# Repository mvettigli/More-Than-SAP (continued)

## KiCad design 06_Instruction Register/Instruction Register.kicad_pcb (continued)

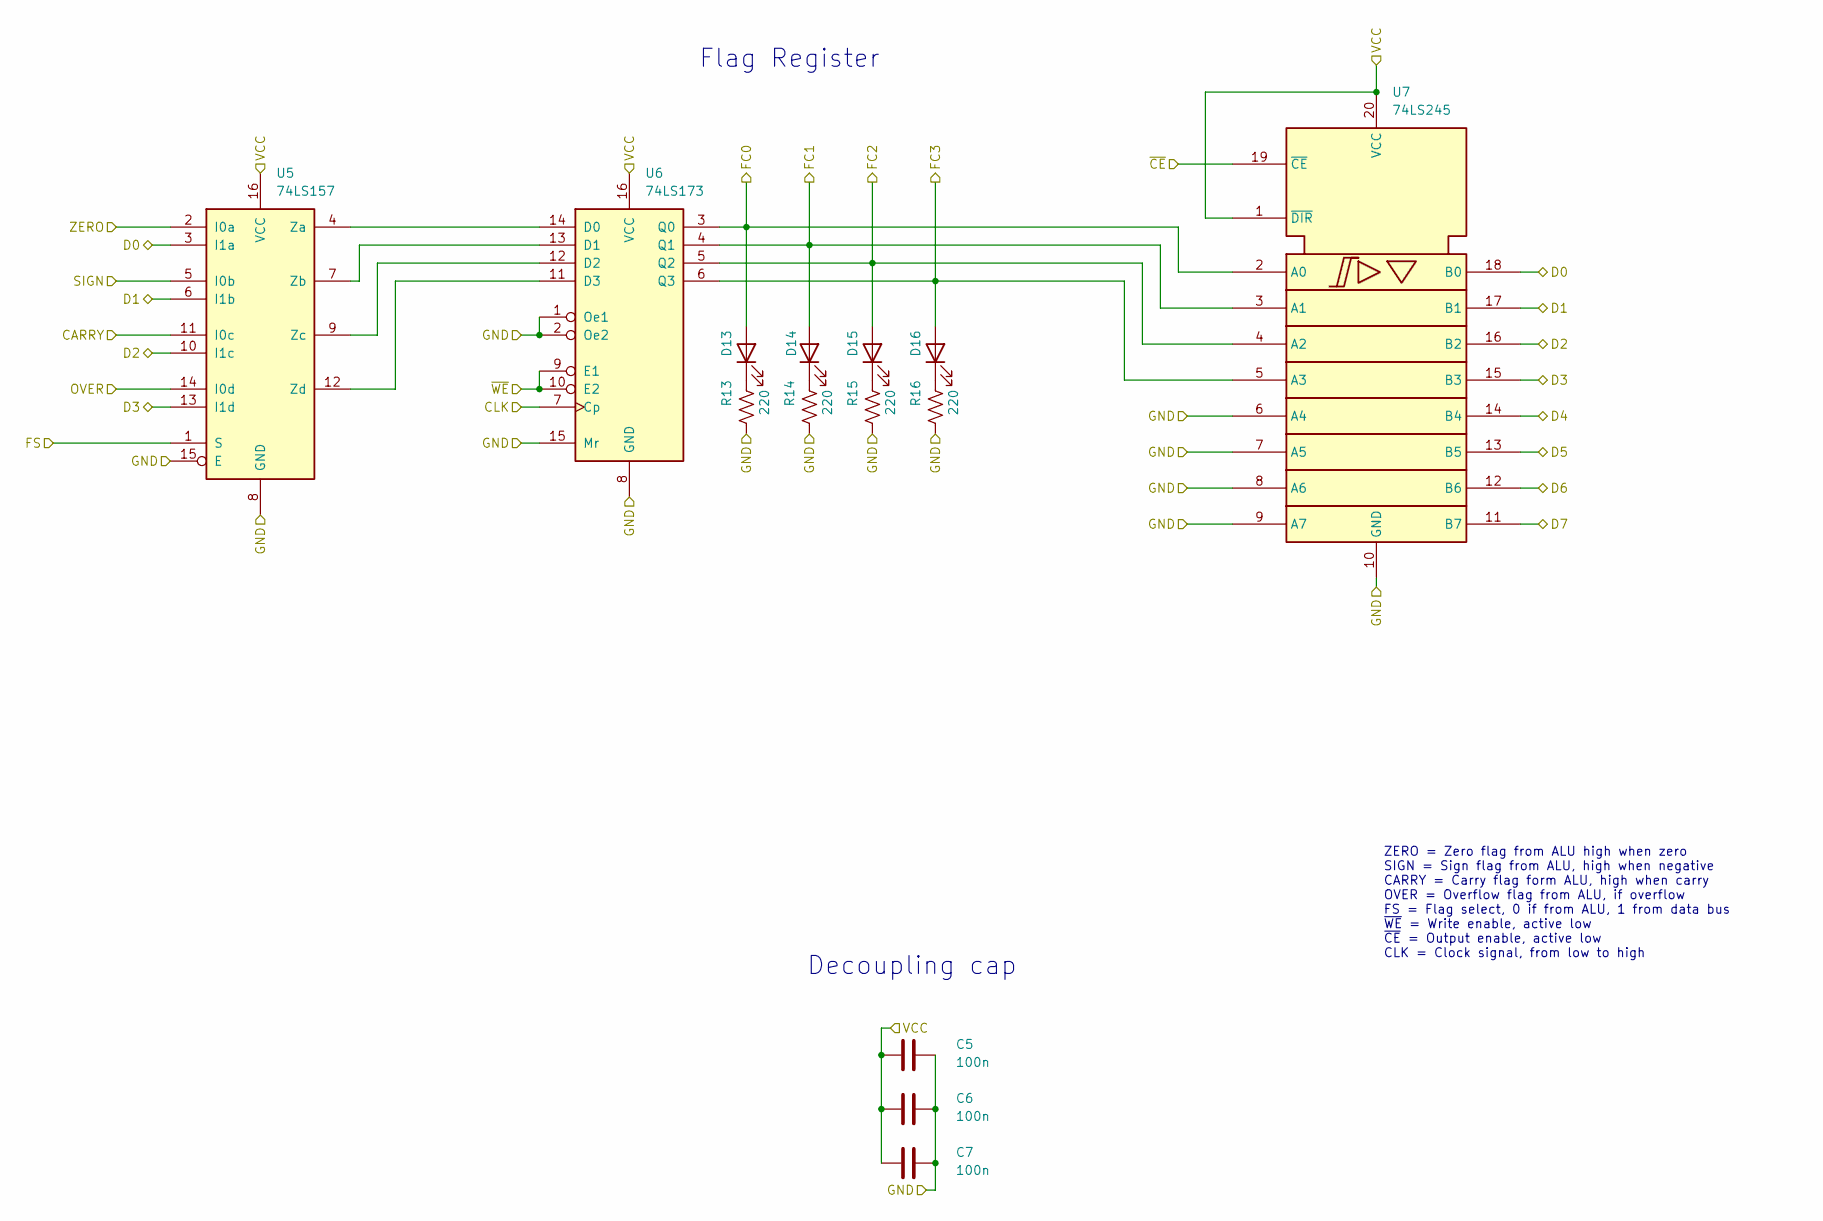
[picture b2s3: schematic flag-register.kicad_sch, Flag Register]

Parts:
C5, C6, C7: 100n; C_Disc_D3.0mm_W1.6mm_P2.50mm
D13, D14, D15, D16: ORA; LED_D3.0mm
R13, R14, R15, R16: 220; R_Axial_DIN0207_L6.3mm_D2.5mm_P10.16mm_Horizontal
U5: 74LS157; DIP-16_W7.62mm
U6: 74LS173; DIP-16_W7.62mm
U7: 74LS245; DIP-20_W7.62mm

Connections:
/D0: U5.3 (I1a), U7.18 (B0); also elsewhere on the board
/D1: U5.6 (I1b), U7.17 (B1); also elsewhere on the board
/D2: U5.10 (I1c), U7.16 (B2); also elsewhere on the board
/D3: U5.13 (I1d), U7.15 (B3); also elsewhere on the board
/D4: U7.14 (B4); also elsewhere on the board
/D5: U7.13 (B5); also elsewhere on the board
/D6: U7.12 (B6); also elsewhere on the board
/D7: U7.11 (B7); also elsewhere on the board
CARRY: U5.11 (I0c); also elsewhere on the board
CLK: U6.7 (Cp); also elsewhere on the board
F0: D13.2 (A), U6.3 (Q0), U7.2 (A0); also elsewhere on the board
F1: D14.2 (A), U6.4 (Q1), U7.3 (A1); also elsewhere on the board
F2: D15.2 (A), U6.5 (Q2), U7.4 (A2); also elsewhere on the board
F3: D16.2 (A), U6.6 (Q3), U7.5 (A3); also elsewhere on the board
FS: U5.1 (S); also elsewhere on the board
GND: C5.2, C6.2, C7.2, R13.2, R14.2, R15.2, R16.2, U5.8 (GND), U5.15 (E), U6.1 (Oe1), U6.2 (Oe2), U6.8 (GND), U6.15 (Mr), U7.6 (A4), U7.7 (A5), U7.8 (A6), U7.9 (A7), U7.10 (GND); also elsewhere on the board
unnamed: D13.1 (K), R13.1
unnamed: D14.1 (K), R14.1
unnamed: D15.1 (K), R15.1
unnamed: D16.1 (K), R16.1
unnamed: U5.4 (Za), U6.14 (D0)
unnamed: U5.7 (Zb), U6.13 (D1)
unnamed: U5.9 (Zc), U6.12 (D2)
unnamed: U5.12 (Zd), U6.11 (D3)
OVER: U5.14 (I0d); also elsewhere on the board
SIGN: U5.5 (I0b); also elsewhere on the board
VCC: C5.1, C6.1, C7.1, U5.16 (VCC), U6.16 (VCC), U7.1 (~DIR), U7.20 (VCC); also elsewhere on the board
ZERO: U5.2 (I0a); also elsewhere on the board
~FRI: U6.9 (E1), U6.10 (E2); also elsewhere on the board
~FRO: U7.19 (~CE); also elsewhere on the board

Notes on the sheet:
Decoupling cap
Flag Register
ZERO = Zero flag from ALU high when zero SIGN = Sign flag from ALU, high when negative CARRY = Carry flag form ALU, high when carry OVER = Overflow flag from ALU, if overflow FS = Flag select, 0 if from ALU, 1 from data bus ~{WE} = Write enable, active low ~{CE} = Output enable, active low CLK = Cl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

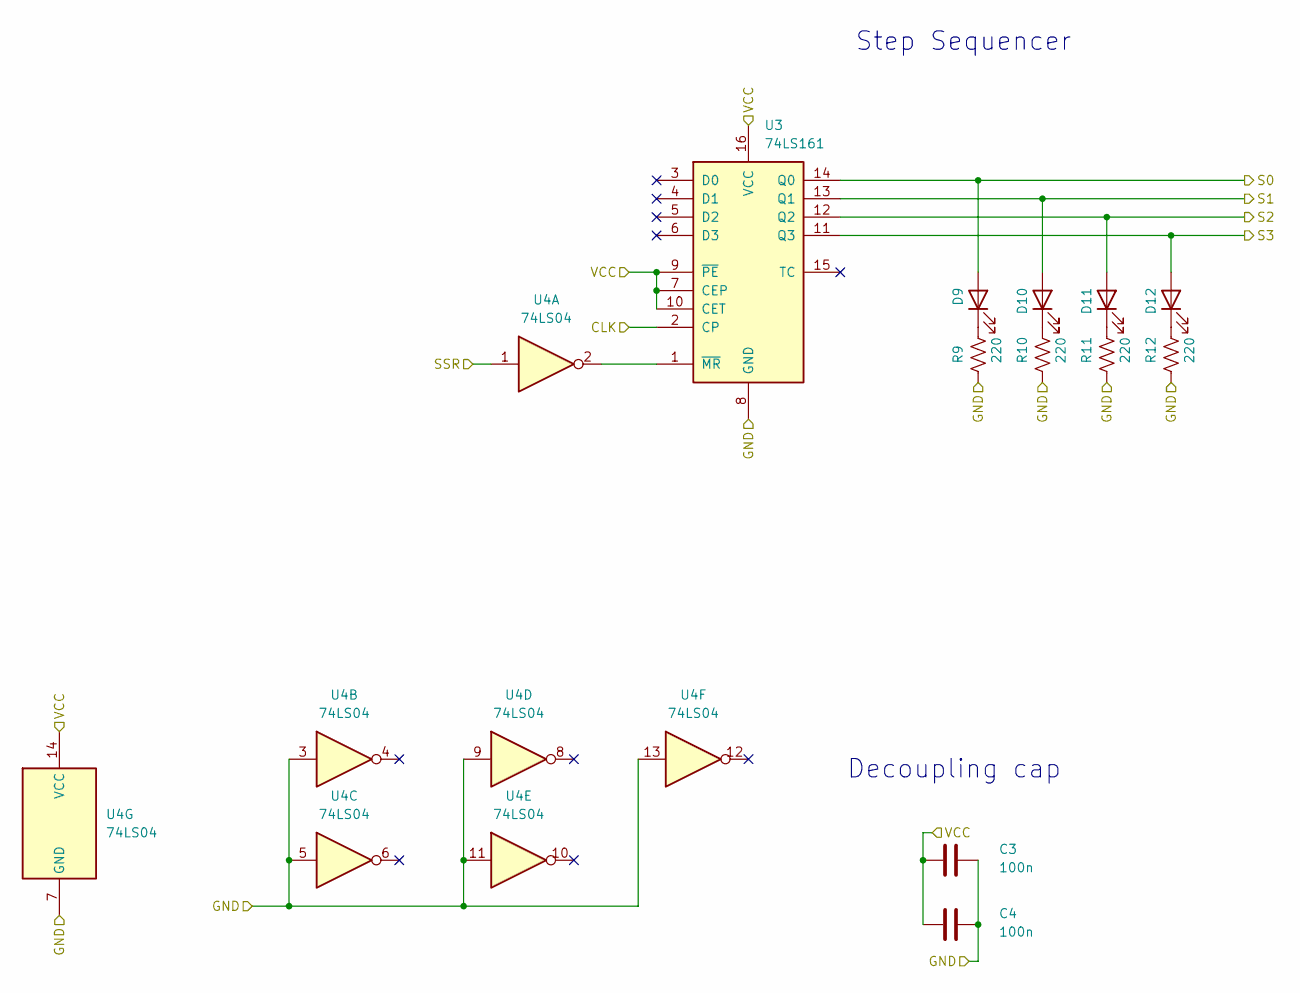
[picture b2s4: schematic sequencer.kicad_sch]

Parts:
C3, C4: 100n; C_Disc_D3.0mm_W1.6mm_P2.50mm
D9, D10, D11, D12: BLU; LED_D3.0mm
R9, R10, R11, R12: 220; R_Axial_DIN0207_L6.3mm_D2.5mm_P10.16mm_Horizontal
U3: 74LS161; DIP-16_W7.62mm
U4: 74LS04; DIP-14_W7.62mm

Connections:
CLK: U3.2 (CP); also elsewhere on the board
GND: C3.2, C4.2, R9.2, R10.2, R11.2, R12.2, U3.8 (GND), U4.3, U4.5, U4.7 (GND), U4.9, U4.11, U4.13; also elsewhere on the board
unnamed: D9.1 (K), R9.1
unnamed: D10.1 (K), R10.1
unnamed: D11.1 (K), R11.1
unnamed: D12.1 (K), R12.1
unnamed: U3.1 (~MR), U4.2
S0: D9.2 (A), U3.14 (Q0); also elsewhere on the board
S1: D10.2 (A), U3.13 (Q1); also elsewhere on the board
S2: D11.2 (A), U3.12 (Q2); also elsewhere on the board
S3: D12.2 (A), U3.11 (Q3); also elsewhere on the board
SSR: U4.1; also elsewhere on the board
VCC: C3.1, C4.1, U3.7 (CEP), U3.9 (~PE), U3.10 (CET), U3.16 (VCC), U4.14 (VCC); also elsewhere on the board

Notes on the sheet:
Step Sequencer
Decoupling cap

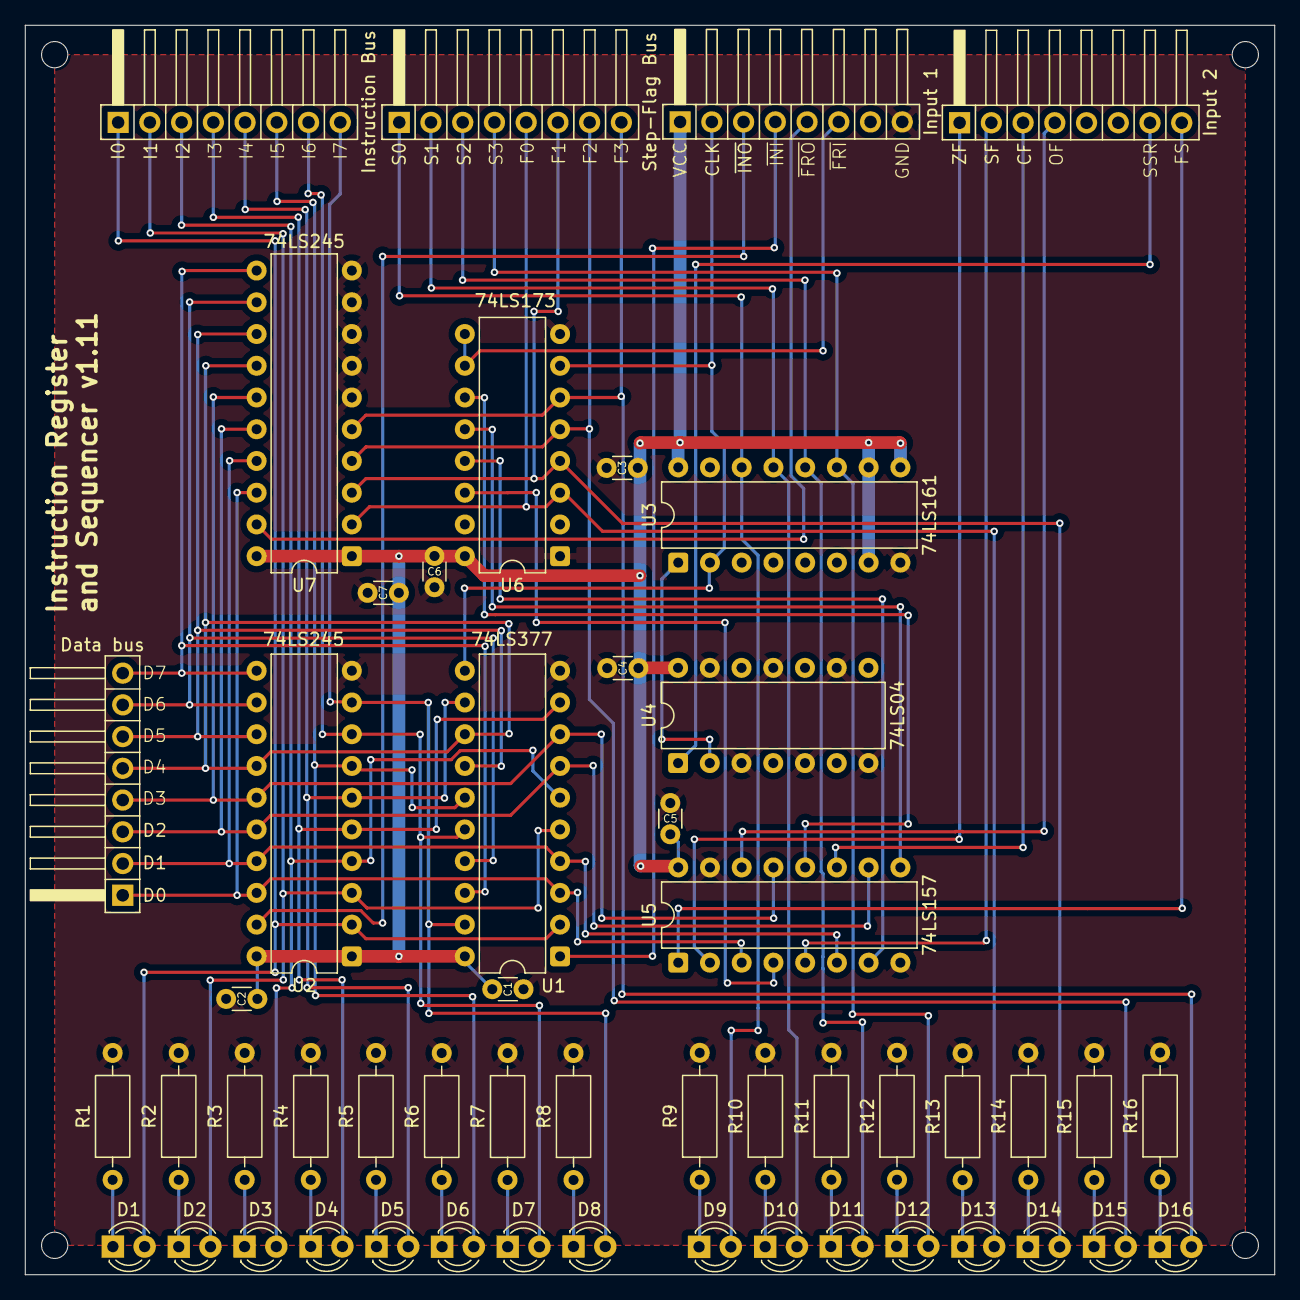
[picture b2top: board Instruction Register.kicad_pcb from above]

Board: 2 copper layers, 100.0 x 100.0 mm, 51 parts (0 on the bottom side), 58 nets.

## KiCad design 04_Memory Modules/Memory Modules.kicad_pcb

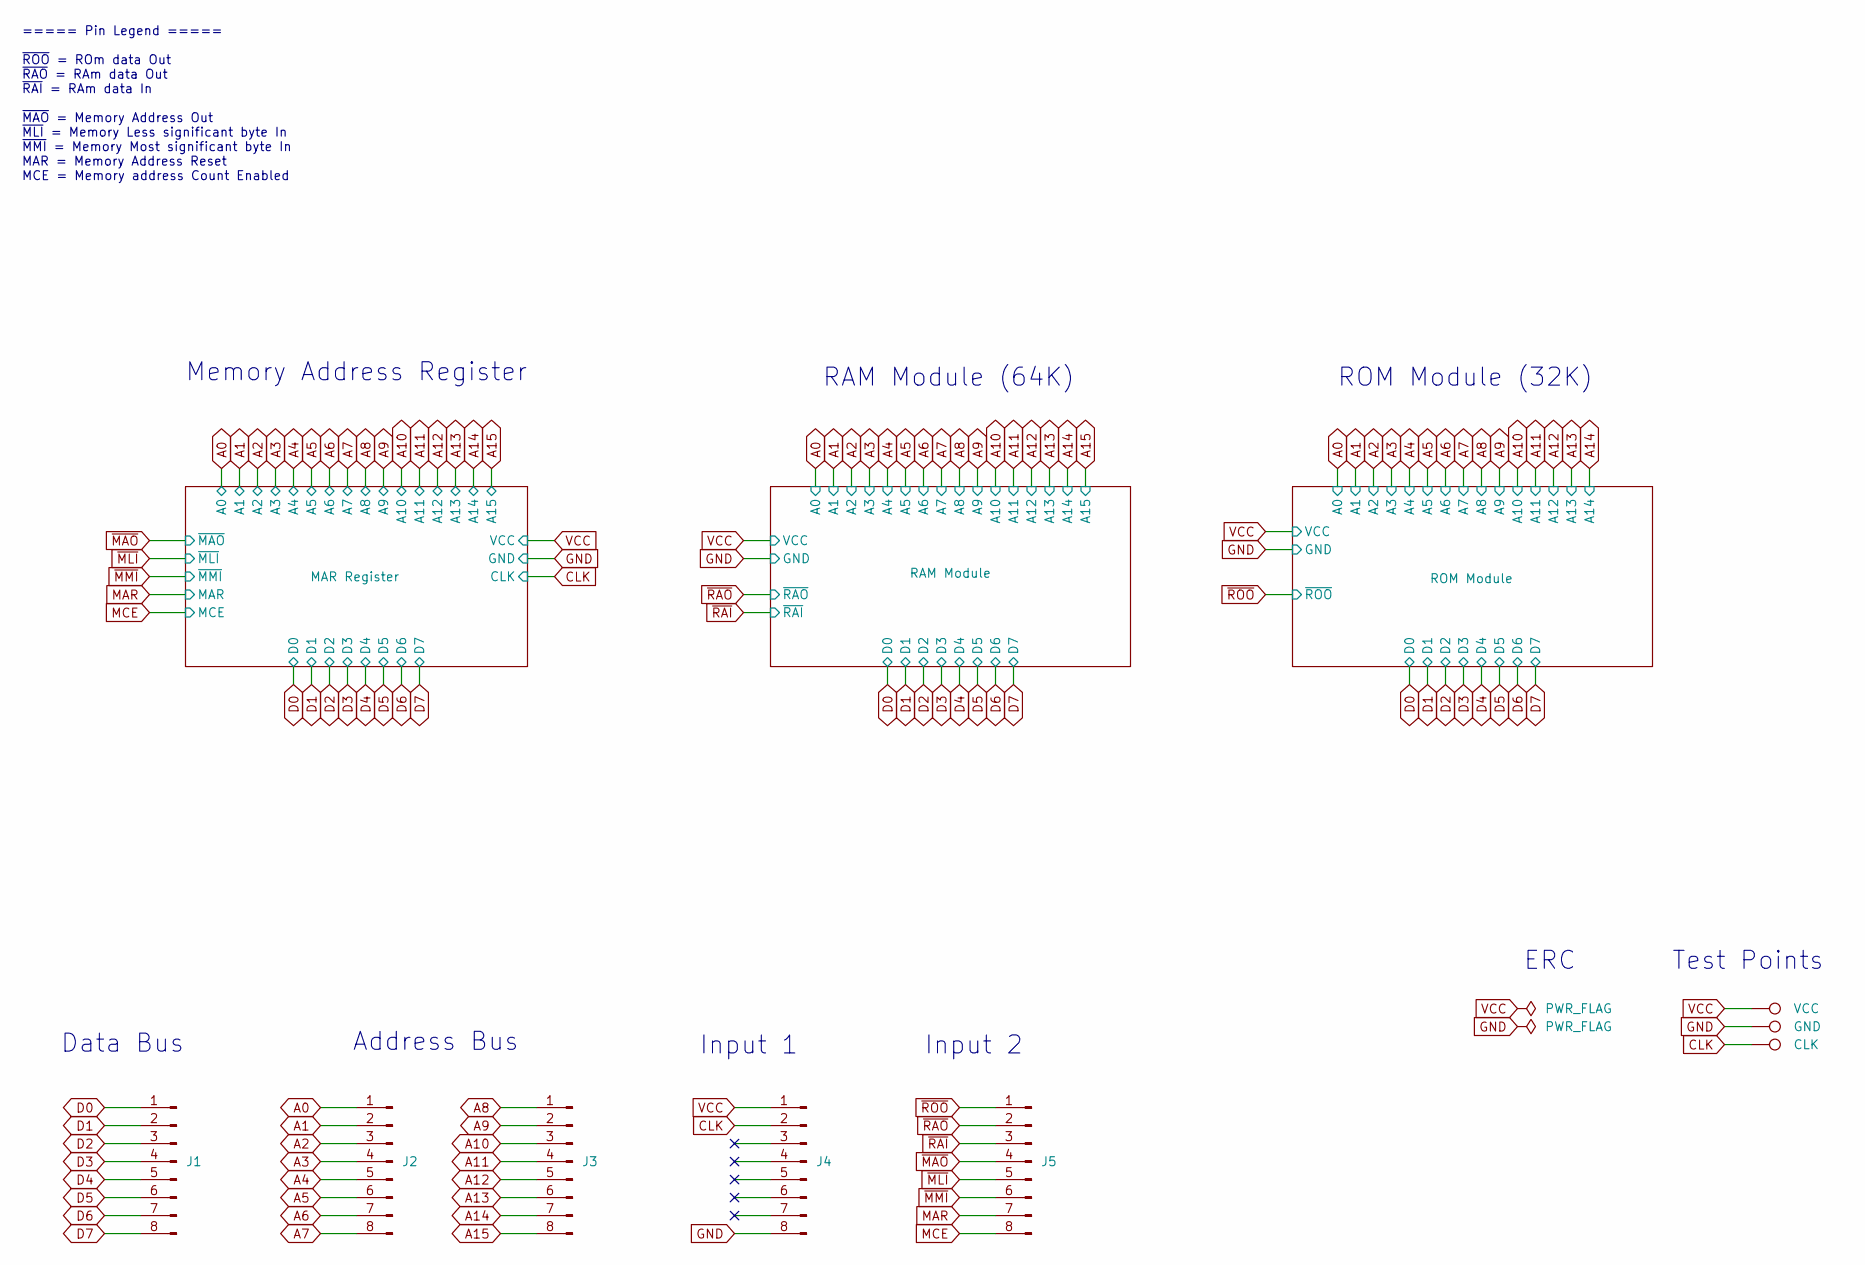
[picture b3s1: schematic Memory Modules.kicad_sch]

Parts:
J1: Data bus; PinHeader_1x08_P2.54mm_Horizontal
J2: Address bus 1; PinHeader_1x08_P2.54mm_Horizontal
J3: Address bus 2; PinHeader_1x08_P2.54mm_Horizontal
J4: Input 1; PinHeader_1x08_P2.54mm_Horizontal
J5: Input 2; PinHeader_1x08_P2.54mm_Horizontal
TP1: GND; TestPoint_Loop_D3.50mm_Drill0.9mm_Beaded
TP2: VCC; TestPoint_Loop_D3.50mm_Drill0.9mm_Beaded
TP3: CLK; TestPoint_Loop_D3.50mm_Drill0.9mm_Beaded

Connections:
A0: J2.1; also elsewhere on the board
A1: J2.2; also elsewhere on the board
A2: J2.3; also elsewhere on the board
A3: J2.4; also elsewhere on the board
A4: J2.5; also elsewhere on the board
A5: J2.6; also elsewhere on the board
A6: J2.7; also elsewhere on the board
A7: J2.8; also elsewhere on the board
A8: J3.1; also elsewhere on the board
A9: J3.2; also elsewhere on the board
A10: J3.3; also elsewhere on the board
A11: J3.4; also elsewhere on the board
A12: J3.5; also elsewhere on the board
A13: J3.6; also elsewhere on the board
A14: J3.7; also elsewhere on the board
A15: J3.8; also elsewhere on the board
CLK: J4.2, TP3.1; also elsewhere on the board
D0: J1.1; also elsewhere on the board
D1: J1.2; also elsewhere on the board
D2: J1.3; also elsewhere on the board
D3: J1.4; also elsewhere on the board
D4: J1.5; also elsewhere on the board
D5: J1.6; also elsewhere on the board
D6: J1.7; also elsewhere on the board
D7: J1.8; also elsewhere on the board
GND: J4.8, TP1.1; also elsewhere on the board
MAR: J5.7; also elsewhere on the board
MCE: J5.8; also elsewhere on the board
VCC: J4.1, TP2.1; also elsewhere on the board
~MAO: J5.4; also elsewhere on the board
~MLI: J5.5; also elsewhere on the board
~MMI: J5.6; also elsewhere on the board
~RAI: J5.3; also elsewhere on the board
~RAO: J5.2; also elsewhere on the board
~ROO: J5.1; also elsewhere on the board

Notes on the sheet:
Memory Address Register
ERC
RAM Module (64K)
Test Points
Address Bus
ROM Module (32K)
Data Bus
Input 2
Input 1
===== Pin Legend ===== ~{ROO} = ROm data Out ~{RAO} = RAm data Out ~{RAI} = RAm data In ~{MAO} = Memory Address Out ~{MLI} = Memory Less significant byte In ~{MMI} = Memory Most significant byte In MAR = Memory Address Reset MCE = Memory address Count Enabled

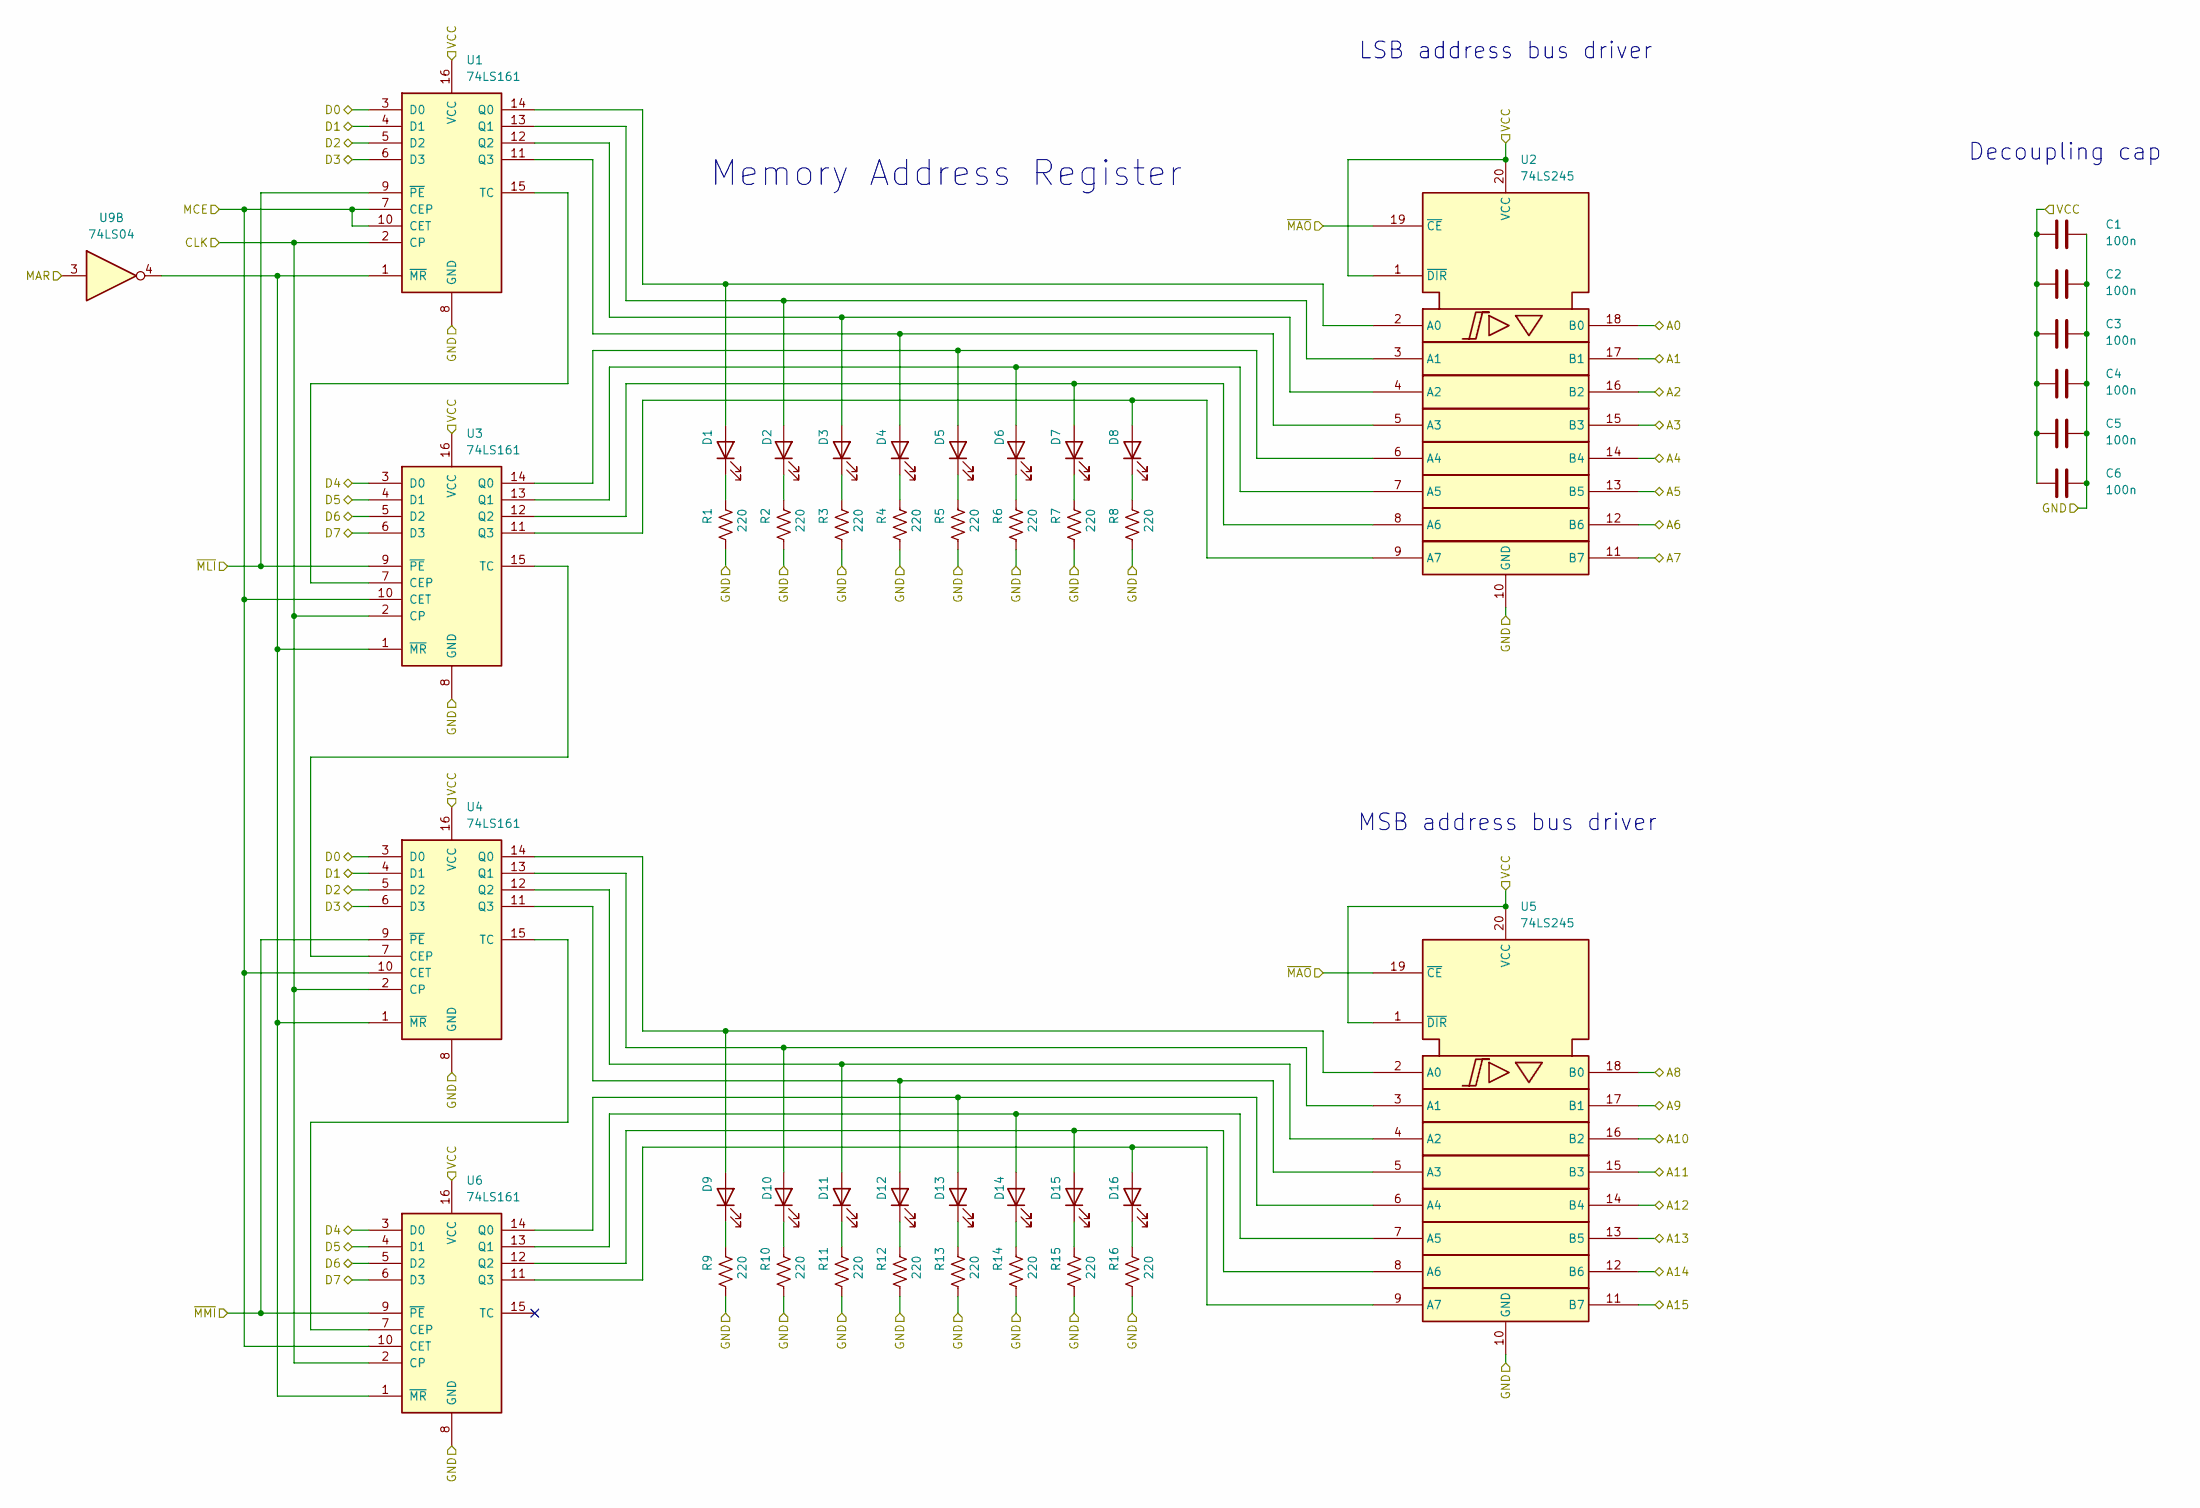
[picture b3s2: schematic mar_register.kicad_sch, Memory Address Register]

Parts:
C1, C2, C3, C4, C5, C6: 100n; C_Disc_D4.7mm_W2.5mm_P5.00mm
D1, D2, D3, D4, D5, D6, D7, D8, D9, D10, D11, D12, D13, D14, D15, D16: GREEN; LED_D3.0mm
R1, R2, R3, R4, R5, R6, R7, R8, R9, R10, R11, R12, R13, R14, R15, R16: 220; R_Axial_DIN0207_L6.3mm_D2.5mm_P10.16mm_Horizontal
U1, U3, U4, U6: 74LS161; DIP-16_W7.62mm
U2, U5: 74LS245; DIP-20_W7.62mm
U9: 74LS04; DIP-14_W7.62mm

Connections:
A0: U2.18 (B0); also elsewhere on the board
A1: U2.17 (B1); also elsewhere on the board
A2: U2.16 (B2); also elsewhere on the board
A3: U2.15 (B3); also elsewhere on the board
A4: U2.14 (B4); also elsewhere on the board
A5: U2.13 (B5); also elsewhere on the board
A6: U2.12 (B6); also elsewhere on the board
A7: U2.11 (B7); also elsewhere on the board
A8: U5.18 (B0); also elsewhere on the board
A9: U5.17 (B1); also elsewhere on the board
A10: U5.16 (B2); also elsewhere on the board
A11: U5.15 (B3); also elsewhere on the board
A12: U5.14 (B4); also elsewhere on the board
A13: U5.13 (B5); also elsewhere on the board
A14: U5.12 (B6); also elsewhere on the board
A15: U5.11 (B7); also elsewhere on the board
CLK: U1.2 (CP), U3.2 (CP), U4.2 (CP), U6.2 (CP); also elsewhere on the board
D0: U1.3 (D0), U4.3 (D0); also elsewhere on the board
D1: U1.4 (D1), U4.4 (D1); also elsewhere on the board
D2: U1.5 (D2), U4.5 (D2); also elsewhere on the board
D3: U1.6 (D3), U4.6 (D3); also elsewhere on the board
D4: U3.3 (D0), U6.3 (D0); also elsewhere on the board
D5: U3.4 (D1), U6.4 (D1); also elsewhere on the board
D6: U3.5 (D2), U6.5 (D2); also elsewhere on the board
D7: U3.6 (D3), U6.6 (D3); also elsewhere on the board
GND: C1.2, C2.2, C3.2, C4.2, C5.2, C6.2, R1.2, R2.2, R3.2, R4.2, R5.2, R6.2, R7.2, R8.2, R9.2, R10.2, R11.2, R12.2, R13.2, R14.2, R15.2, R16.2, U1.8 (GND), U2.10 (GND), U3.8 (GND), U4.8 (GND), U5.10 (GND), U6.8 (GND); also elsewhere on the board
MAR: U9.3; also elsewhere on the board
MCE: U1.7 (CEP), U1.10 (CET), U3.10 (CET), U4.10 (CET), U6.10 (CET); also elsewhere on the board
unnamed: D1.2 (A), U1.14 (Q0), U2.2 (A0)
unnamed: D1.1 (K), R1.1
unnamed: D2.2 (A), U1.13 (Q1), U2.3 (A1)
unnamed: D2.1 (K), R2.1
unnamed: D3.2 (A), U1.12 (Q2), U2.4 (A2)
unnamed: D3.1 (K), R3.1
unnamed: D4.2 (A), U1.11 (Q3), U2.5 (A3)
unnamed: D4.1 (K), R4.1
unnamed: D5.2 (A), U2.6 (A4), U3.14 (Q0)
unnamed: D5.1 (K), R5.1
unnamed: D6.2 (A), U2.7 (A5), U3.13 (Q1)
unnamed: D6.1 (K), R6.1
unnamed: D7.2 (A), U2.8 (A6), U3.12 (Q2)
unnamed: D7.1 (K), R7.1
unnamed: D8.2 (A), U2.9 (A7), U3.11 (Q3)
unnamed: D8.1 (K), R8.1
unnamed: D9.2 (A), U4.14 (Q0), U5.2 (A0)
unnamed: D9.1 (K), R9.1
unnamed: D10.2 (A), U4.13 (Q1), U5.3 (A1)
unnamed: D10.1 (K), R10.1
unnamed: D11.2 (A), U4.12 (Q2), U5.4 (A2)
unnamed: D11.1 (K), R11.1
unnamed: D12.2 (A), U4.11 (Q3), U5.5 (A3)
unnamed: D12.1 (K), R12.1
unnamed: D13.2 (A), U5.6 (A4), U6.14 (Q0)
unnamed: D13.1 (K), R13.1
unnamed: D14.2 (A), U5.7 (A5), U6.13 (Q1)
unnamed: D14.1 (K), R14.1
unnamed: D15.2 (A), U5.8 (A6), U6.12 (Q2)
unnamed: D15.1 (K), R15.1
unnamed: D16.2 (A), U5.9 (A7), U6.11 (Q3)
unnamed: D16.1 (K), R16.1
unnamed: U1.15 (TC), U3.7 (CEP)
unnamed: U1.1 (~MR), U3.1 (~MR), U4.1 (~MR), U6.1 (~MR), U9.4
unnamed: U3.15 (TC), U4.7 (CEP)
unnamed: U4.15 (TC), U6.7 (CEP)
VCC: C1.1, C2.1, C3.1, C4.1, C5.1, C6.1, U1.16 (VCC), U2.1 (~DIR), U2.20 (VCC), U3.16 (VCC), U4.16 (VCC), U5.1 (~DIR), U5.20 (VCC), U6.16 (VCC); also elsewhere on the board
~MAO: U2.19 (~CE), U5.19 (~CE); also elsewhere on the board
~MLI: U1.9 (~PE), U3.9 (~PE); also elsewhere on the board
~MMI: U4.9 (~PE), U6.9 (~PE); also elsewhere on the board

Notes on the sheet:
Decoupling cap
MSB address bus driver
LSB address bus driver
Memory Address Register

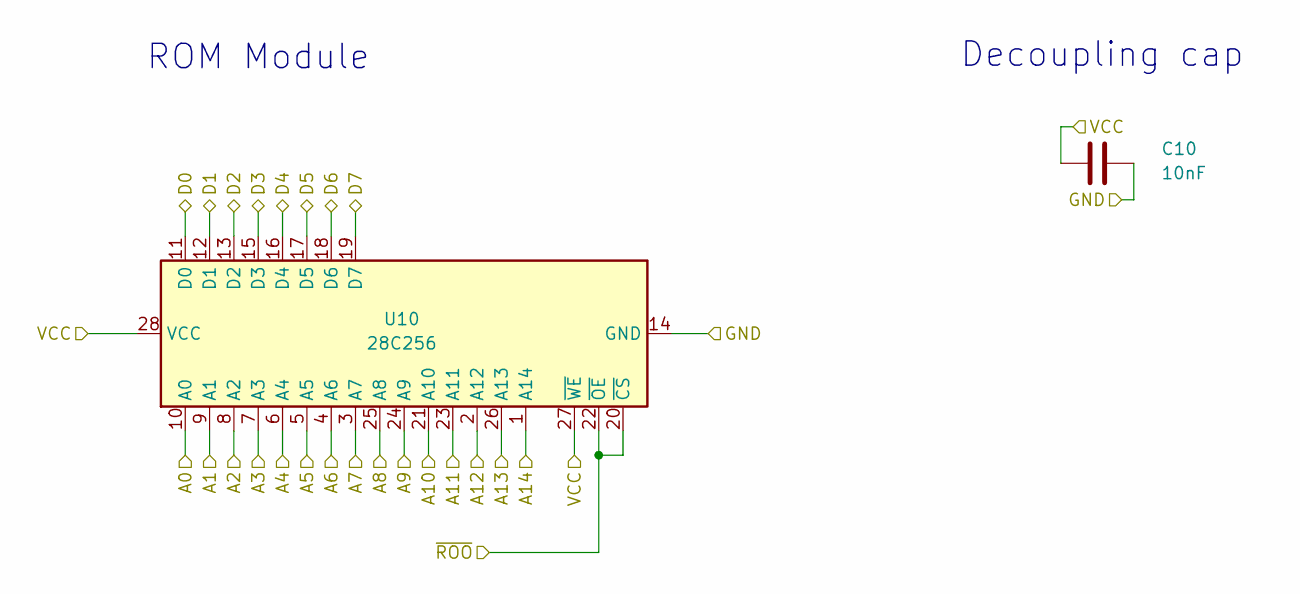
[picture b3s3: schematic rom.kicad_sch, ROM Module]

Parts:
C10: 10nF; C_Disc_D4.7mm_W2.5mm_P5.00mm
U10: 28C256; DIP-28_W15.24mm_Socket_LongPads

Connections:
A0: U10.10 (A0); also elsewhere on the board
A1: U10.9 (A1); also elsewhere on the board
A2: U10.8 (A2); also elsewhere on the board
A3: U10.7 (A3); also elsewhere on the board
A4: U10.6 (A4); also elsewhere on the board
A5: U10.5 (A5); also elsewhere on the board
A6: U10.4 (A6); also elsewhere on the board
A7: U10.3 (A7); also elsewhere on the board
A8: U10.25 (A8); also elsewhere on the board
A9: U10.24 (A9); also elsewhere on the board
A10: U10.21 (A10); also elsewhere on the board
A11: U10.23 (A11); also elsewhere on the board
A12: U10.2 (A12); also elsewhere on the board
A13: U10.26 (A13); also elsewhere on the board
A14: U10.1 (A14); also elsewhere on the board
D0: U10.11 (D0); also elsewhere on the board
D1: U10.12 (D1); also elsewhere on the board
D2: U10.13 (D2); also elsewhere on the board
D3: U10.15 (D3); also elsewhere on the board
D4: U10.16 (D4); also elsewhere on the board
D5: U10.17 (D5); also elsewhere on the board
D6: U10.18 (D6); also elsewhere on the board
D7: U10.19 (D7); also elsewhere on the board
GND: C10.2, U10.14 (GND); also elsewhere on the board
VCC: C10.1, U10.27 (~WE), U10.28 (VCC); also elsewhere on the board
~ROO: U10.20 (~CS), U10.22 (~OE); also elsewhere on the board

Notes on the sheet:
ROM Module
Decoupling cap

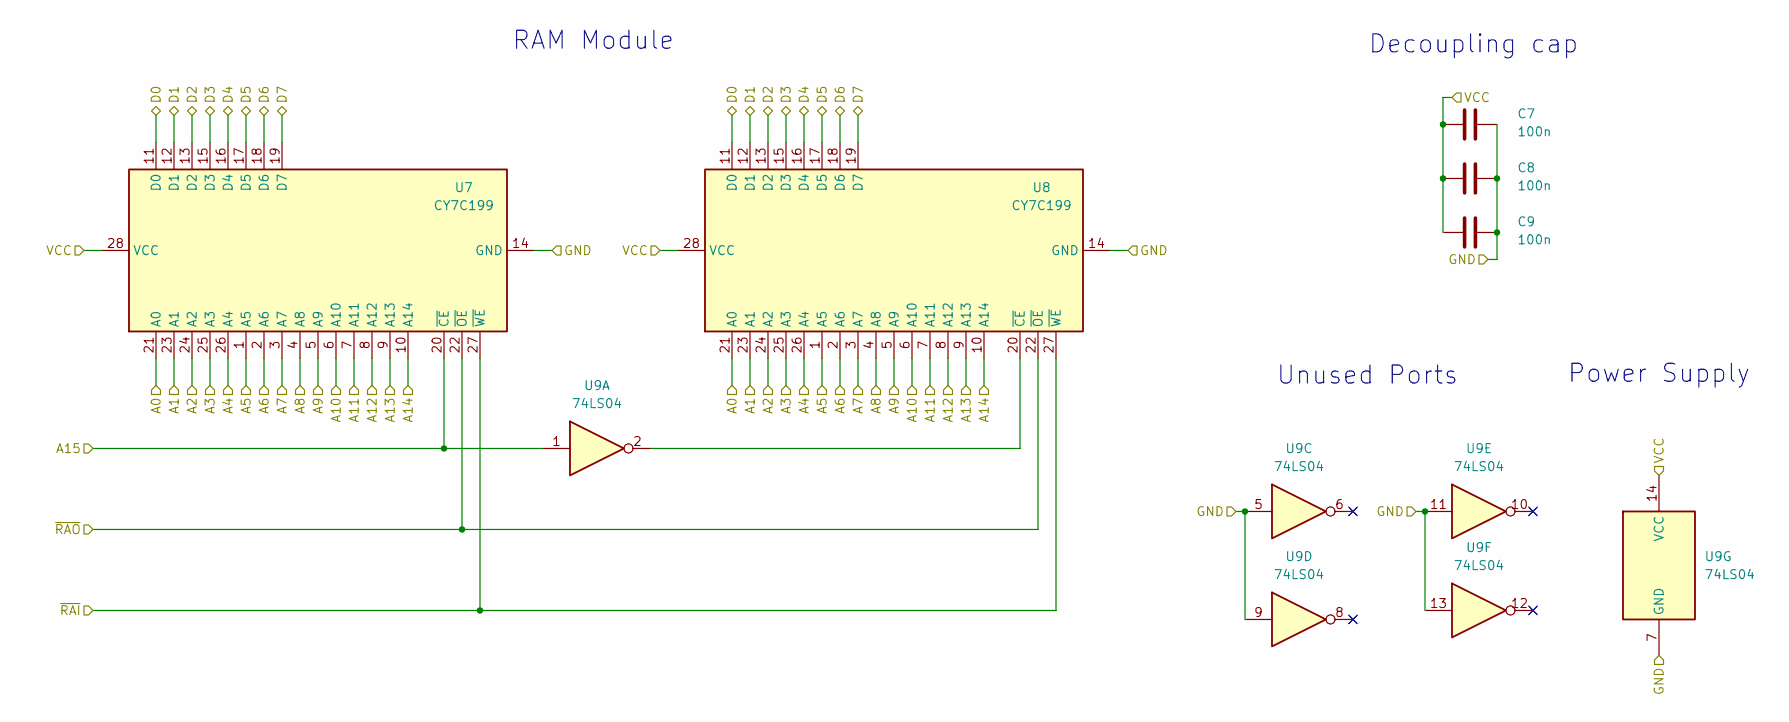
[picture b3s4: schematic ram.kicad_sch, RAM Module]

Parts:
C7, C8, C9: 100n; C_Disc_D4.7mm_W2.5mm_P5.00mm
U7, U8: CY7C199; DIP-28_W7.62mm
U9: 74LS04; DIP-14_W7.62mm

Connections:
A0: U7.21 (A0), U8.21 (A0); also elsewhere on the board
A1: U7.23 (A1), U8.23 (A1); also elsewhere on the board
A2: U7.24 (A2), U8.24 (A2); also elsewhere on the board
A3: U7.25 (A3), U8.25 (A3); also elsewhere on the board
A4: U7.26 (A4), U8.26 (A4); also elsewhere on the board
A5: U7.1 (A5), U8.1 (A5); also elsewhere on the board
A6: U7.2 (A6), U8.2 (A6); also elsewhere on the board
A7: U7.3 (A7), U8.3 (A7); also elsewhere on the board
A8: U7.4 (A8), U8.4 (A8); also elsewhere on the board
A9: U7.5 (A9), U8.5 (A9); also elsewhere on the board
A10: U7.6 (A10), U8.6 (A10); also elsewhere on the board
A11: U7.7 (A11), U8.7 (A11); also elsewhere on the board
A12: U7.8 (A12), U8.8 (A12); also elsewhere on the board
A13: U7.9 (A13), U8.9 (A13); also elsewhere on the board
A14: U7.10 (A14), U8.10 (A14); also elsewhere on the board
A15: U7.20 (~CE), U9.1; also elsewhere on the board
D0: U7.11 (D0), U8.11 (D0); also elsewhere on the board
D1: U7.12 (D1), U8.12 (D1); also elsewhere on the board
D2: U7.13 (D2), U8.13 (D2); also elsewhere on the board
D3: U7.15 (D3), U8.15 (D3); also elsewhere on the board
D4: U7.16 (D4), U8.16 (D4); also elsewhere on the board
D5: U7.17 (D5), U8.17 (D5); also elsewhere on the board
D6: U7.18 (D6), U8.18 (D6); also elsewhere on the board
D7: U7.19 (D7), U8.19 (D7); also elsewhere on the board
GND: C7.2, C8.2, C9.2, U7.14 (GND), U8.14 (GND), U9.5, U9.7 (GND), U9.9, U9.11, U9.13; also elsewhere on the board
unnamed: U8.20 (~CE), U9.2
VCC: C7.1, C8.1, C9.1, U7.28 (VCC), U8.28 (VCC), U9.14 (VCC); also elsewhere on the board
~RAI: U7.27 (~WE), U8.27 (~WE); also elsewhere on the board
~RAO: U7.22 (~OE), U8.22 (~OE); also elsewhere on the board

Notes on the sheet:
Decoupling cap
RAM Module
Unused Ports
Power Supply

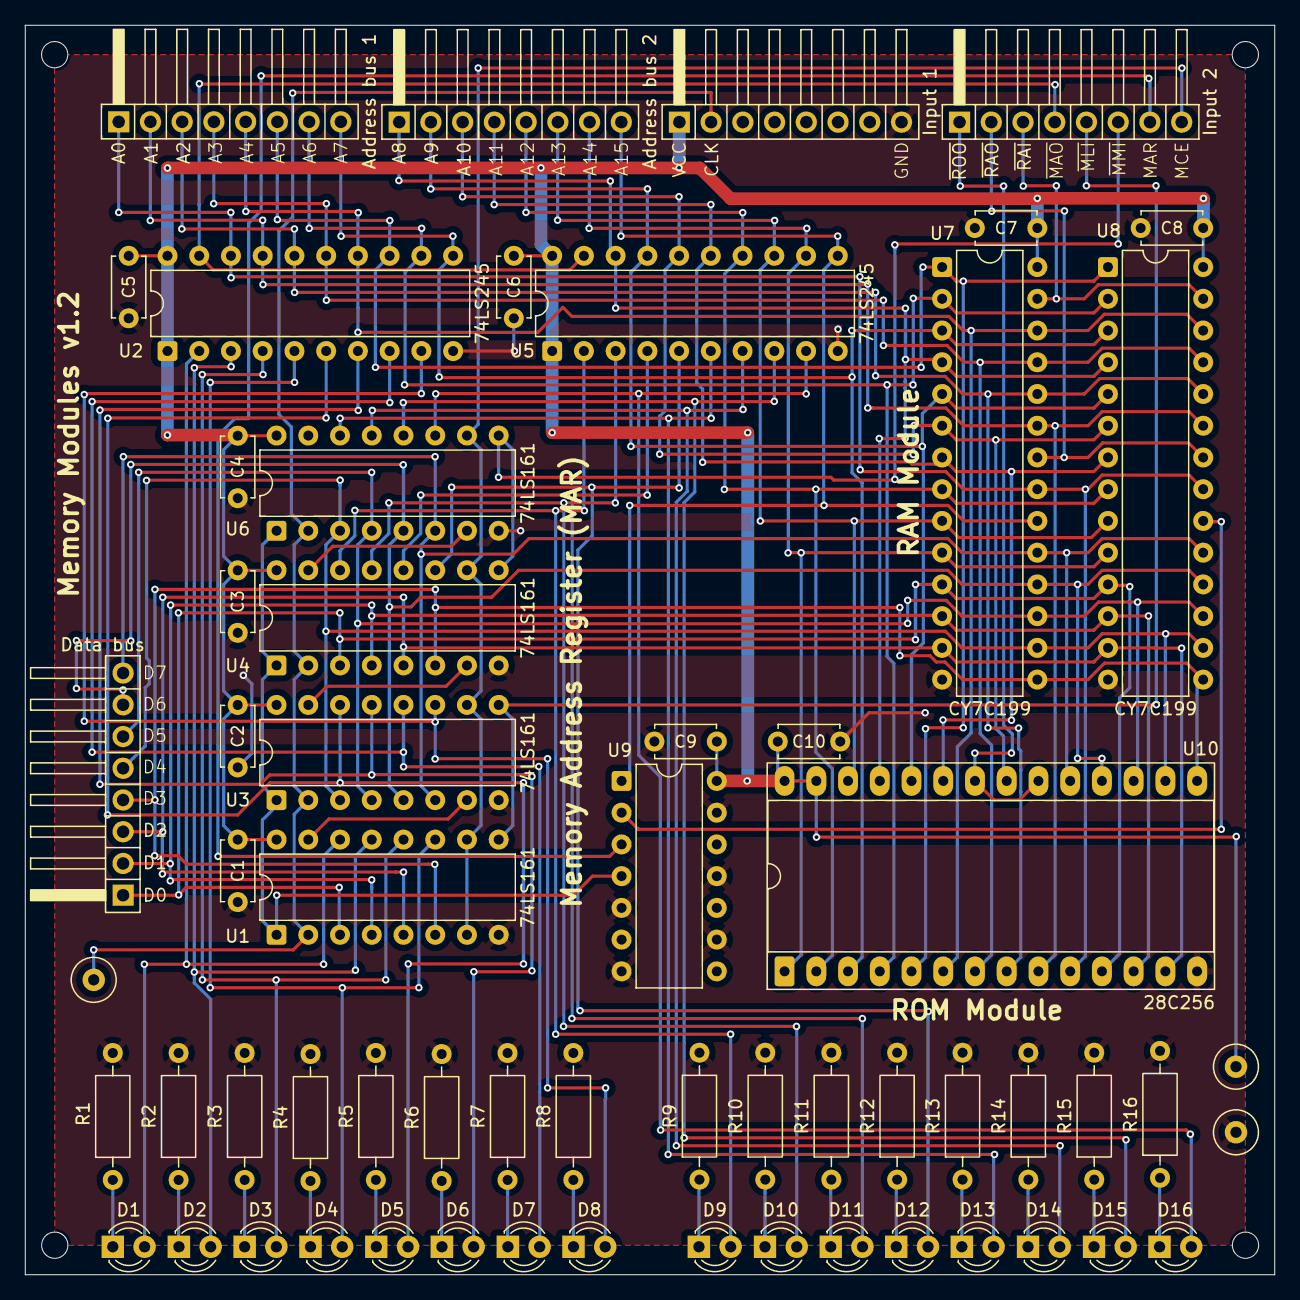
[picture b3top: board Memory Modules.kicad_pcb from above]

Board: 2 copper layers, 100.0 x 100.0 mm, 60 parts (0 on the bottom side), 72 nets.
